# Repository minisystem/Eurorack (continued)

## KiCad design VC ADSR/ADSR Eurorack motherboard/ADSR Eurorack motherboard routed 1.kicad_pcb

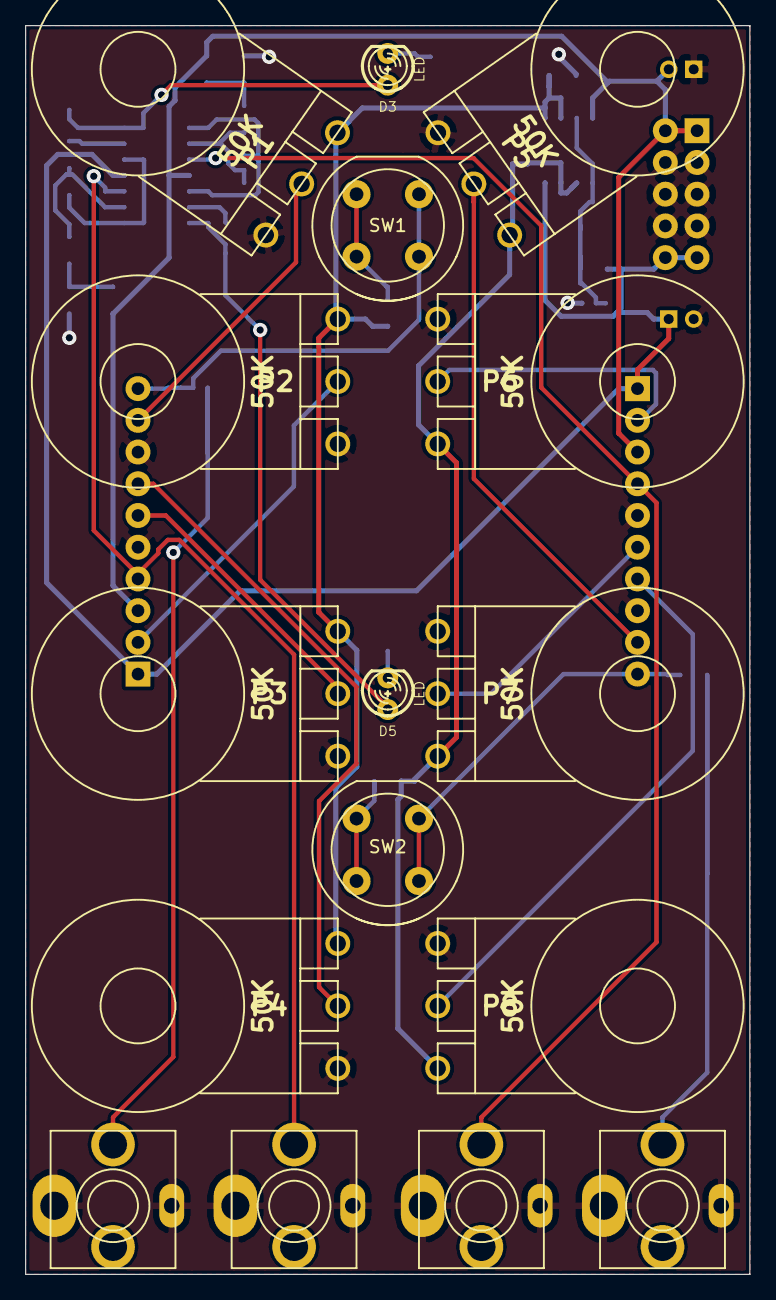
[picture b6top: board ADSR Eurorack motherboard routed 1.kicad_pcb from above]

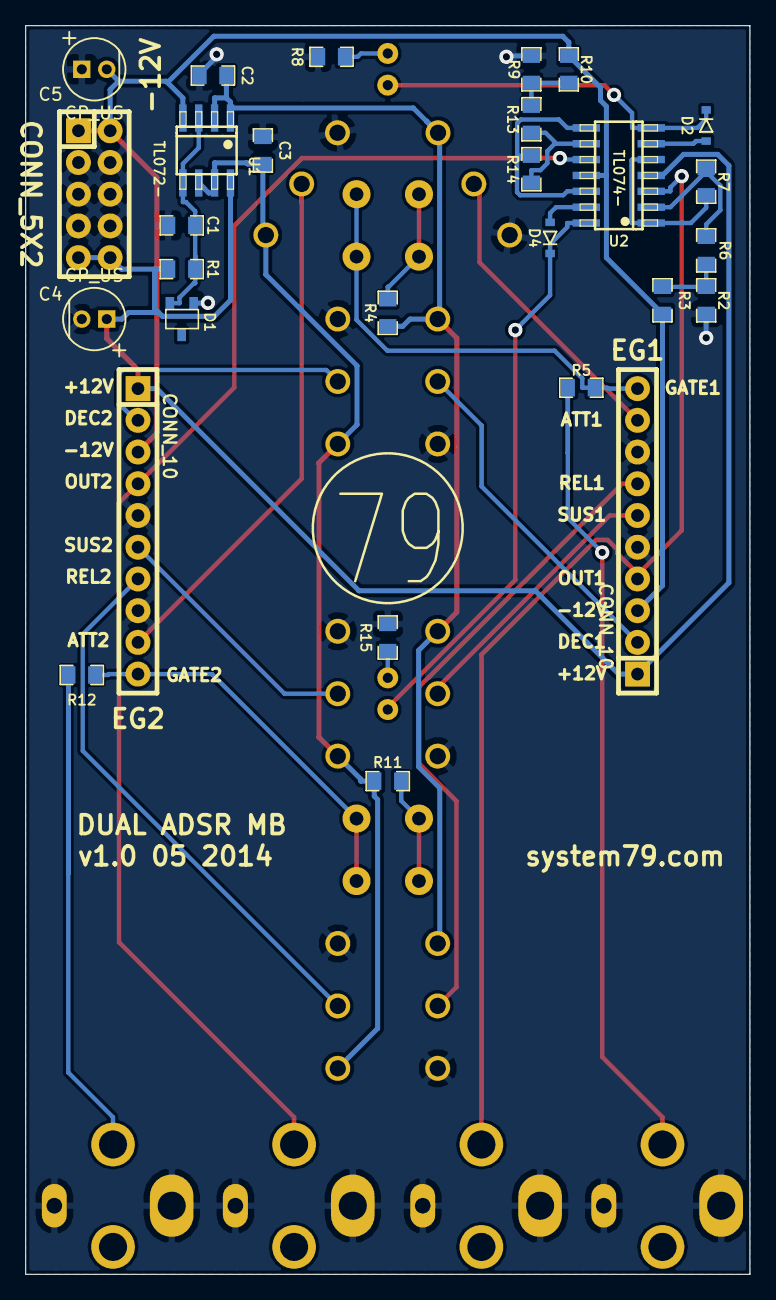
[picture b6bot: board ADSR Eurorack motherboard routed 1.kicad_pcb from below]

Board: 2 copper layers, 58.0 x 100.0 mm, 45 parts (29 on the bottom side), 34 nets.

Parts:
C1, C2, C3: 100n; SM0805-HAND
C4, C5: CP_US; CAP_POL_5MM
D1: LM4040-5.0; SOT23-JRL
D2, D4: 1N4148; SOD323-JRL
D3, D5: LED; LED-3MM
EG1, EG2: CONN_10; CONN_0100_X_10
J1, J3: OUT1; PJ-301B-JACK
J2, J4: GATE1; PJ-301B-JACK
P1, P2, P3, P4, P5, P6, P7, P8: 50K; RV16A-41-JRL
PWR1: CONN_5X2; CONN_0100_2X5_10
R1, R4, R5, R11, R12: 10K; SM0805-HAND
R2, R9: 120K; SM0805-HAND
R3, R10: 330K; SM0805-HAND
R6, R13: 100K; SM0805-HAND
R7, R14: 82K; SM0805-HAND
R8, R15: 270; SM0805-HAND
SW1, SW2: SW_PUSH; KS-01Q-02-JRL
U1: TL072-; SOIC-8-JRL
U2: TL074-; SO14-JRL
system79-logo-12mm: VAL**; system79-logo-12mm

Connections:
+5.0V A: C2.1, P1.3, P2.3, P3.3, P4.3, R4.1, U1.1, U1.2
+5.0V B: C3.1, P5.3, P6.3, P7.3, P8.3, R11.1, U1.6, U1.7
+12V: C4.1, EG1.1, EG2.1, PWR1.9, PWR1.10, R1.1, U1.8, U2.4
-12V: C5.2, EG1.3, EG2.3, PWR1.1, PWR1.2, R3.1, R10.1, U1.4, U2.11
ATT1: EG1.9, P1.2
ATT2: EG2.9, P5.2
DEC1: EG1.2, P2.2
DEC2: EG2.2, P6.2
GATE1: EG1.10, R5.2, SW1.2, SW1.4
GATE2: EG2.10, R12.2, SW2.2, SW2.4
GND: C1.2, C2.2, C3.2, C4.2, C5.1, D1.2, EG1.5, EG1.8, EG2.5, EG2.8, J1.1, J2.1, J3.1, J4.1, P1.1, P2.1, P3.1, P4.1, P5.1, P6.1, P7.1, P8.1, PWR1.3, PWR1.4, PWR1.5, PWR1.6, PWR1.7, PWR1.8, R2.2, R8.1, R9.2, R15.1
unnamed: R11.2, SW2.1, SW2.3
unnamed: R2.1, R3.2, R6.1
unnamed: R6.2, R7.1, U2.2
unnamed: R13.2, R14.1, U2.9
unnamed: D4.2, D5.1, U2.14
unnamed: D5.2, R15.2
unnamed: D4.1, U2.13
unnamed: R4.2, SW1.1, SW1.3
unnamed: J4.3, R12.1
unnamed: R9.1, R10.2, R13.1
unnamed: R14.2, U2.8, U2.12
unnamed: J2.3, R5.1
unnamed: D2.1, U2.6
unnamed: R7.2, U2.1, U2.5
unnamed: C1.1, D1.1, R1.2, U1.3, U1.5
unnamed: D2.2, D3.1, U2.7
unnamed: D3.2, R8.2
OUT1: EG1.4, J1.3, U2.3
OUT2: EG2.4, J3.3, U2.10
REL1: EG1.7, P4.2
REL2: EG2.7, P8.2
SUS1: EG1.6, P3.2
SUS2: EG2.6, P7.2

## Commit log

2014-12-29 first add Eurorack repository
2015-04-07 fixed Eurorack VCA CV gain pot. Was reversed. Now v1.1. Ordered updated PCBs from DirtyPCBs.com
2015-04-07 added Corrected Eurorack VCA motherboard v1.1 gerbers folder
